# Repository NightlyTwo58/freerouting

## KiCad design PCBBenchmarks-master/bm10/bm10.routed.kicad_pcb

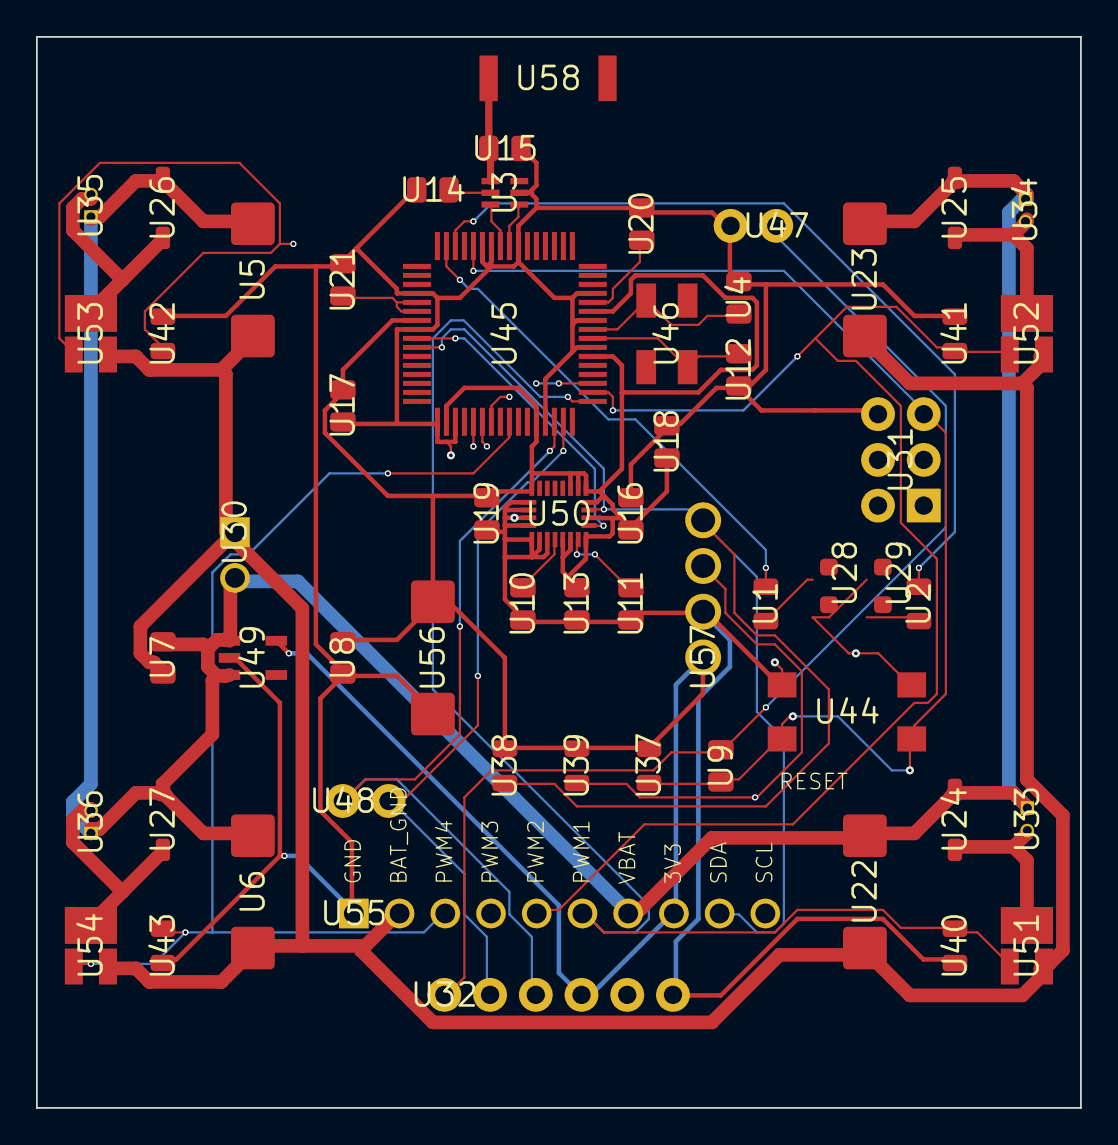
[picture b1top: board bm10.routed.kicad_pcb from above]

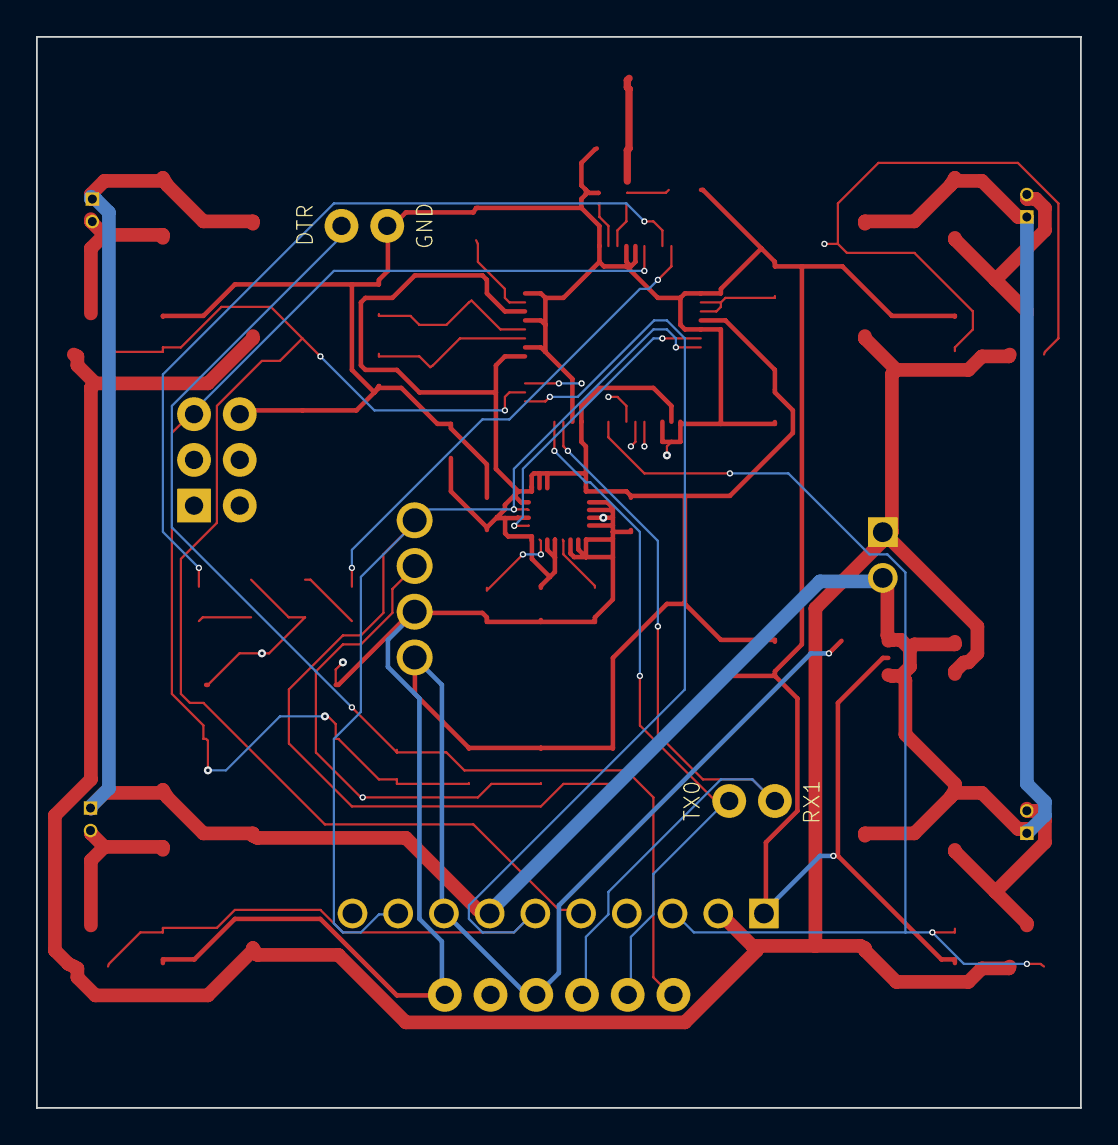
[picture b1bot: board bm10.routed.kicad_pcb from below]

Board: 4 copper layers, 58.0 x 59.5 mm, 58 parts (2 on the bottom side), 35 nets.

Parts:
U1, U2, U37, U38, U39, U40, U41, U42, U43: RESC2012X60_HS
U3: BALUN
U4, U7, U8, U9, U10, U11, U12, U13, U14, U15, U16, U17, U18, U19, U20, U21: CAPC2012X140_HS
U5, U6, U22, U23, U56: CAPMP7343X310_HS
U24, U25, U26, U27: SOD3716X135_HS
U28, U29: LEDSC125X200X120-2_HS
U30: MALE_HEADER_2X1_0.1IN
U31: 2X3-NS
U32: FTDI_BASIC
U33, U34, U35, U36: MOLEX-0530470210
U44: 4.5MM_TACTILE_SWITCH_TL3305AF160QG
U45: QFN-64
U46: CRYSTAL-SMD-5X3
U47: FTDI_BASIC_2PIN_2
U48: FTDI_BASIC_2PIN_1
U49: SOT23-DBV
U50: NEW_IMU_MEDIUM
U51, U52, U53, U54: N_FET_SI2302CDS-T1-E3CT-ND
U55: HDRV10W63P254_10X1_2540X254H838_HS
U57: HDRVR4W80P254_1X4_1066X254X850B
U58: ANT-2.4GHZ-6.5X2.2MM

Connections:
3V3: U8.1, U13.1, U16.1, U17.1, U18.1, U19.1, U32.VCC, U37.2, U38.2, U39.2, U45.23, U45.34, U45.44, U45.54, U45.59, U49.5, U50.CS_A/G, U50.CS_M, U50.DEN_A/G, U50.SDO_A/G, U50.SDO_M, U50.VDD1, U50.VDD2, U50.VDDIO, U50.VDDIO2, U55.8, U56.1, U57.1
/DTR: U9.1, U32.DTR, U47.DTR
/LED1: U2.2, U45.14
/LED2: U1.2, U45.15
/MISO: U31.1, U45.39
/MOSI: U31.4, U45.38
/PWM1: U40.1, U45.49, U51.G, U55.6
/PWM2: U41.1, U45.50, U52.G, U55.5
/PWM3: U42.1, U45.51, U53.G, U55.4
/PWM4: U43.1, U45.41, U54.G, U55.3
/RESET: U9.2, U31.5, U37.1, U44.3, U44.4, U45.12
/RX0: U32.TXO, U45.46, U48.TXO
/SCK: U31.3, U45.37
/SCL: U39.1, U45.25, U50.SCL/SPC, U55.10, U57.3
/SDA: U38.1, U45.26, U50.SDA/SDI/SDO, U55.9, U57.4
/TX0: U32.RXI, U45.47, U48.RXI
BAT_GND: U5.2, U6.2, U7.2, U22.2, U23.2, U30.1, U51.S, U52.S, U53.S, U54.S, U55.2
GND: U3.5, U4.2, U8.2, U10.2, U11.2, U12.2, U13.2, U14.2, U15.2, U16.2, U17.2, U18.2, U19.2, U20.2, U21.2, U28.2, U29.1, U31.6, U32.GND, U40.2, U41.2, U42.2, U43.2, U44.1, U44.2, U45.7, U45.10, U45.11, U45.20, U45.24, U45.33, U45.35, U45.45, U45.55, U45.58, U45.61, U47.CTS, U49.2, U50.GND1, U50.GND2, U50.RES1, U50.RES2, U50.RES3, U50.RES4, U50.RES5, U55.1, U56.2, U57.2
unnamed: U3.1, U15.1, U58.FEED
unnamed: U3.2, U14.1
unnamed: U3.3, U45.9
unnamed: U3.4, U45.8
unnamed: U4.1, U45.57, U46.1
unnamed: U12.1, U45.56, U46.3
unnamed: U20.1, U45.60
unnamed: U21.1, U45.21, U45.22
unnamed: U10.1, U50.CAP
unnamed: U11.1, U50.C1
unnamed: U24.A, U33.2, U51.D
unnamed: U25.A, U34.2, U52.D
unnamed: U26.A, U35.2, U53.D
unnamed: U27.A, U36.2, U54.D
unnamed: U1.1, U28.1
unnamed: U2.1, U29.2
VBAT: U5.1, U6.1, U7.1, U22.1, U23.1, U24.C, U25.C, U26.C, U27.C, U30.2, U33.1, U34.1, U35.1, U36.1, U49.1, U49.3, U55.7

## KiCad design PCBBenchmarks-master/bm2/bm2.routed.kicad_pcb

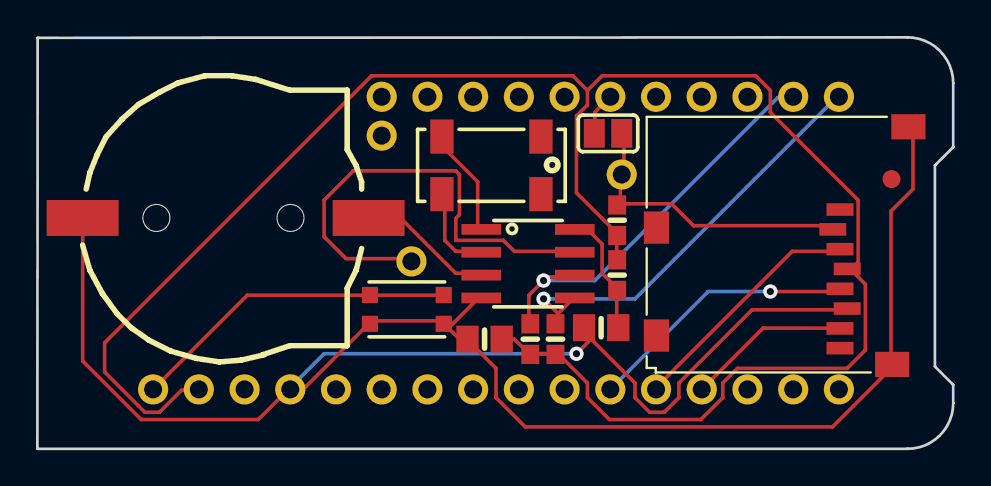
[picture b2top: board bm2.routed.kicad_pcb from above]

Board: 2 copper layers, 50.9 x 22.9 mm, 18 parts (0 on the bottom side), 15 nets.

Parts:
B1: cr1220; CR1220-2
C1, C2: 10uF; 0805-NO
FID1: FIDUCIAL_1MM
IC1: PCF8523T; SOIC8_150MIL
INT1: 1X01_ROUND
JP1: 1X11_ROUND
JP2: 1X16_ROUND
JP3: 1X01_ROUND
R1, R2: 10K; 0603-NO
R3: 100K; 0603-NO
R4: 1K; 0603-NO
SDCS: 1X01_ROUND
SJ1: SOLDERJUMPER_CLOSEDWIRE
SW1: KMR2; BTN_KMR2_4.6X2.8
X4: microsd; MICROSD
Y1: 32khz; CRYSTAL_8X3.8

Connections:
+3V3: C2.1, JP2.15, R1.2, R2.2, R3.2, R4.1, X4.4
CR1220: B1.+, IC1.3
CS: JP1.6, SJ1.1
GND: B1.-, C1.2, C2.2, IC1.4, JP2.13, SW1.A, SW1.A', X4.6, X4.MT1, X4.MT2
INT1: IC1.7, INT1.1
MISO: JP2.4, X4.7
MOSI: JP2.5, X4.3
unnamed: C1.1, IC1.8, R4.2
unnamed: IC1.1, Y1.P$4
unnamed: IC1.2, Y1.P$1
RESET: JP2.16, SW1.B, SW1.B'
SCK: JP2.6, X4.5
SCL: IC1.6, JP1.10, R2.1
SDA: IC1.5, JP1.11, R1.1
SD_CS: R3.1, SDCS.1, SJ1.2, X4.2

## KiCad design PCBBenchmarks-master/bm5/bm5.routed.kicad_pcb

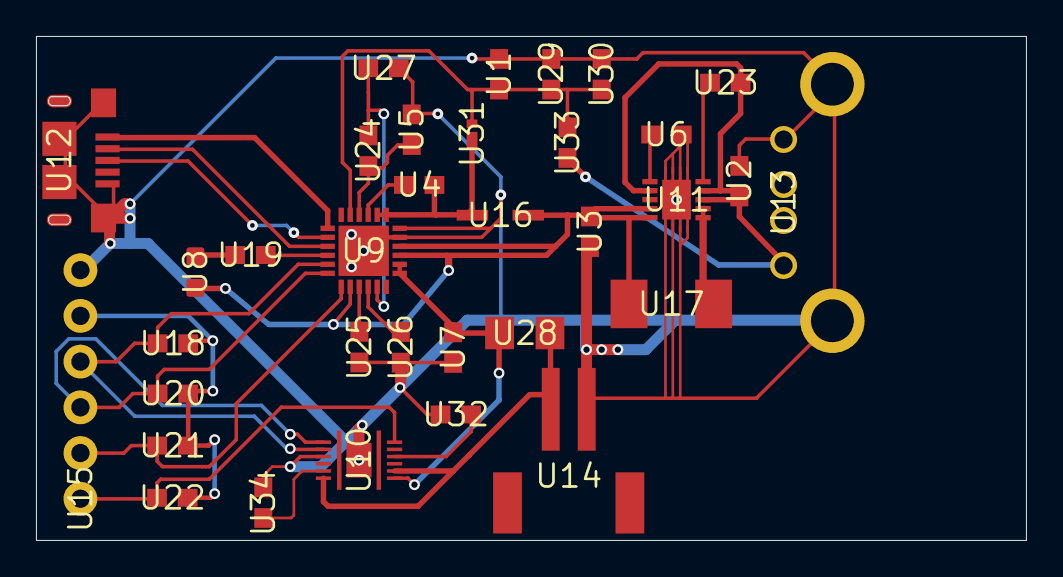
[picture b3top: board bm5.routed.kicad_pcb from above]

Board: 2 copper layers, 55.0 x 28.0 mm, 34 parts (0 on the bottom side), 27 nets.

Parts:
U1, U2, U3, U4, U5, U6, U7, U18, U19, U20, U21, U22, U23, U24, U25, U26, U27, U29, U30, U32, U33, U34: 0603
U8: LED-0603
U9: QFN50P400X400X100-25N
U10: BQ27441DRZRG1A
U11: SON50P300X300X100-11N
U12: 10118193-0001LF
U13: UE27AC54100
U14: JST-2-SMD
U15: 1X06
U16: INDPM3630X200N
U17: INDPM5552X200N
U28: 1206
U31: DSN2_1

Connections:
3.3V: U15.5, U18.2, U20.2, U21.2, U22.2
5V: U2.1, U11.3, U11.4, U11.7, U13.1, U23.1, U33.2
/CHG_INT: U9.7, U15.2, U21.1
/FUEL_INT: U10.12, U15.1, U22.1
/REG: U5.1, U9.22, U24.1
/SCL: U9.5, U10.2, U15.4, U18.1
/SDA: U9.6, U10.1, U15.3, U20.1
/VBAT_CELL: U7.1, U9.13, U9.14, U10.7, U28.1
/VBAT_MAIN: U3.1, U8.A, U9.8, U9.15, U9.16, U11.9, U11.10, U16.2, U17.1
GND: U1.2, U2.2, U3.2, U5.2, U6.2, U7.2, U9.17, U9.18, U9.25, U10.3, U10.13, U11.GND@1, U11.GND@2, U11.GND@3, U11.GND@4, U11.GND@5, U11.GND@6, U11.GND@7, U11.GND@8, U11.GND@9, U12.GND, U12.SHIELD$1, U12.SHIELD$2, U12.SHIELD$3, U12.SHIELD$4, U13.4, U13.5, U13.6, U14.1, U15.6, U25.1, U26.1, U27.1, U29.2, U30.2, U32.1, U34.2
unnamed: U4.1, U9.19, U9.20, U16.1, U31.2
unnamed: U4.2, U9.21
unnamed: U1.1, U9.23, U29.1, U30.1, U31.1, U33.1
unnamed: U6.1, U11.6
unnamed: U10.5, U34.1
unnamed: U8.C, U19.1
unnamed: U9.1, U12.VCC
unnamed: U9.2, U12.D+
unnamed: U9.3, U12.D-
unnamed: U9.4, U19.2
unnamed: U9.9, U25.2
unnamed: U9.10, U26.2
unnamed: U9.11, U24.2, U27.2
unnamed: U10.6, U10.8, U14.2, U28.2
unnamed: U10.10, U32.2
unnamed: U11.1, U11.2, U17.2
unnamed: U11.5, U23.2
